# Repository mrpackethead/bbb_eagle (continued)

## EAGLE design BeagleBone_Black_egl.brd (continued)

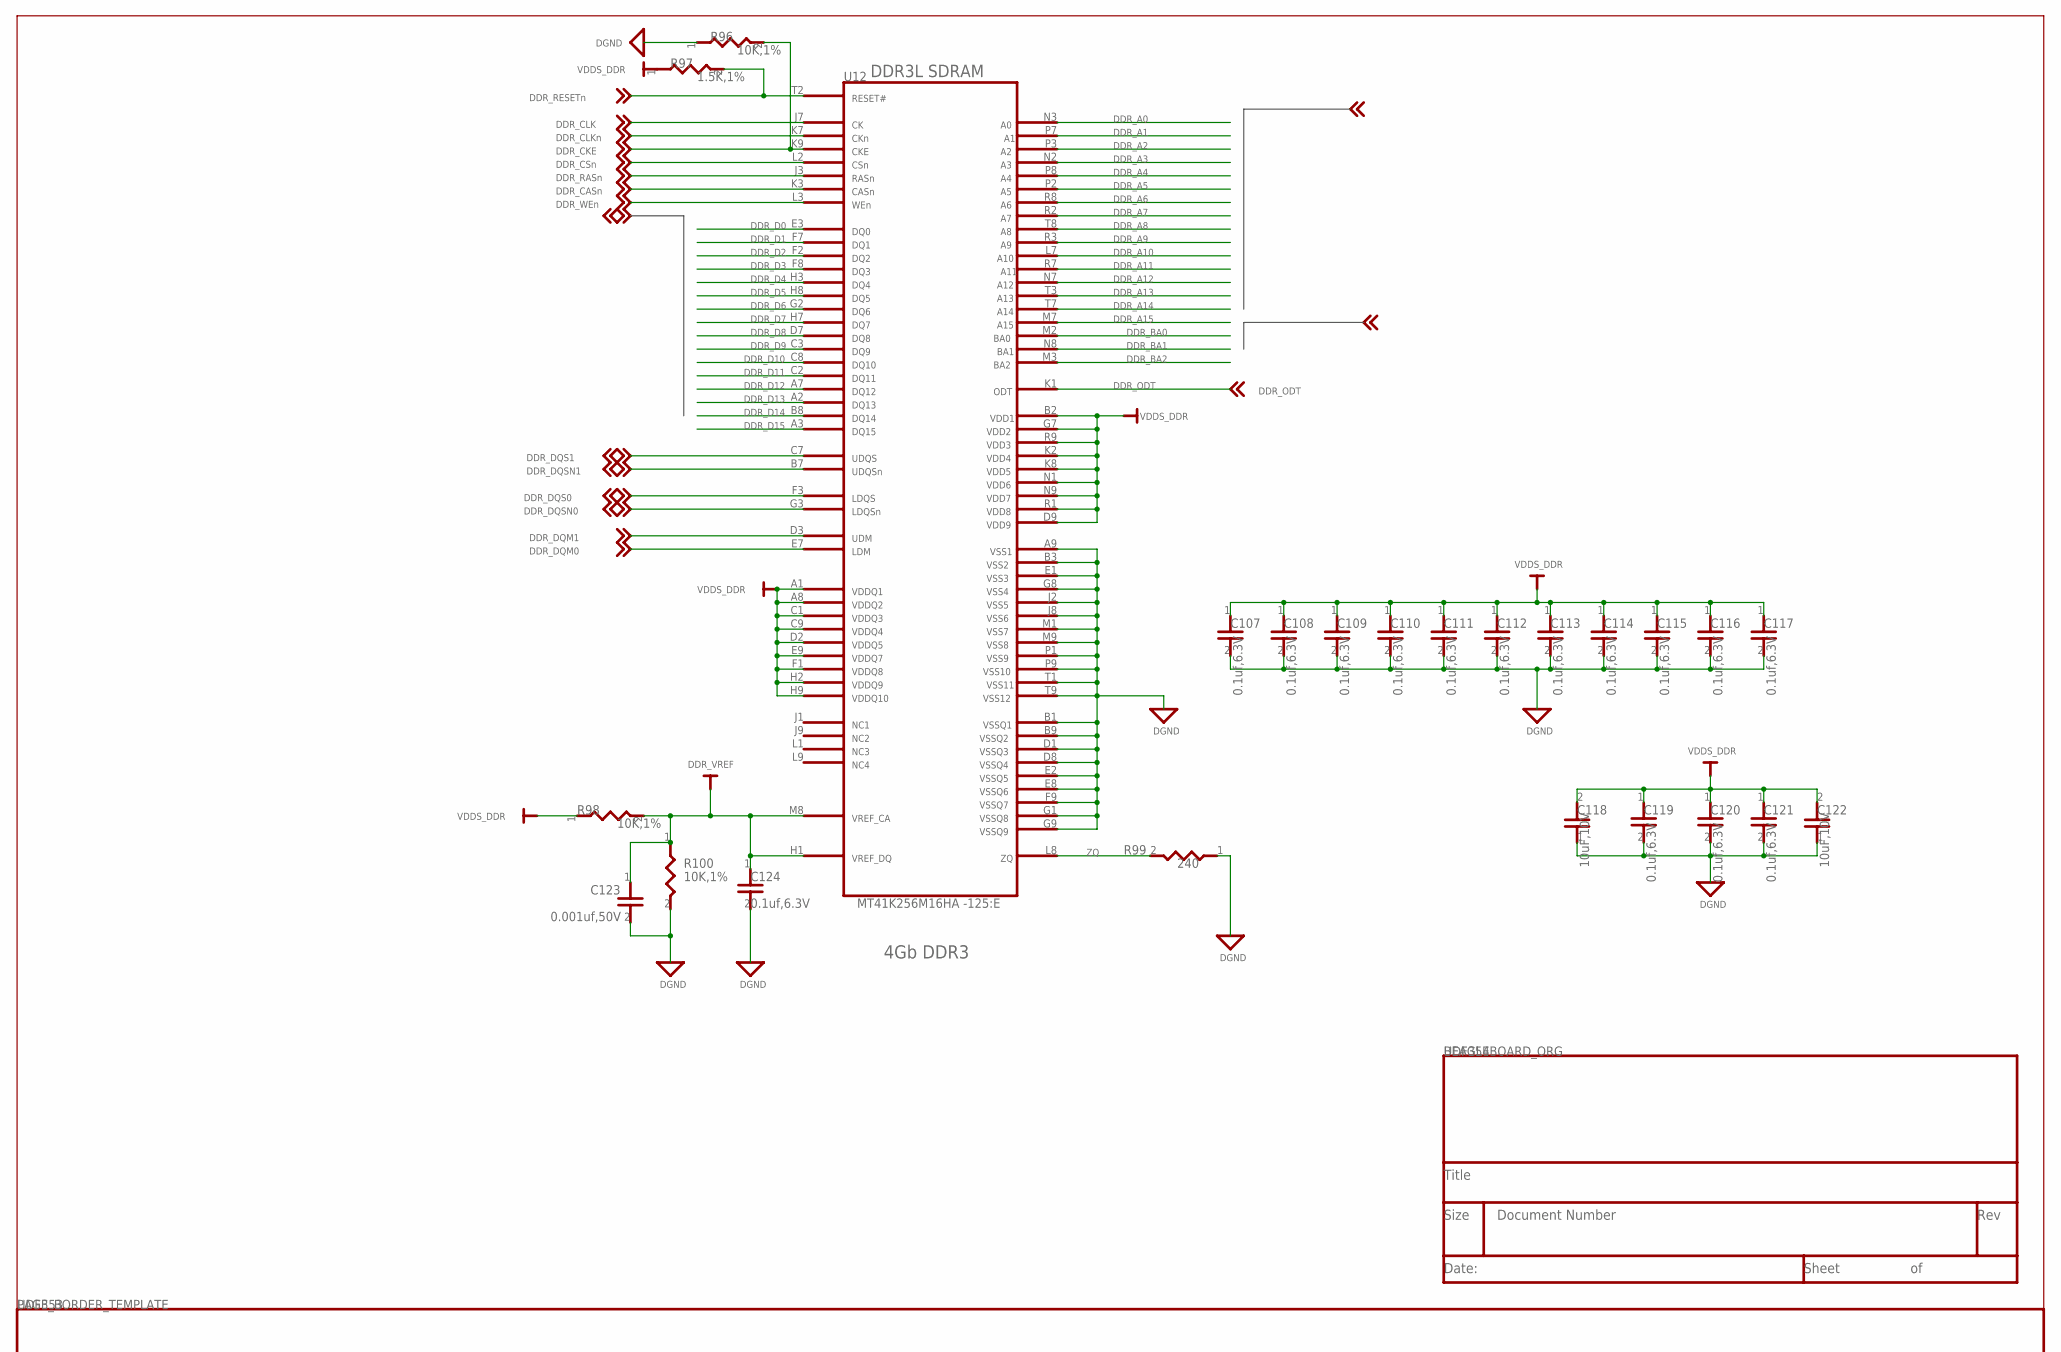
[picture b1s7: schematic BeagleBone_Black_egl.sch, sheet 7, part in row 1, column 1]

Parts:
C107, C108, C109, C110, C111, C112, C113, C114, C115, C116, C117, C119, C120, C121, C124: 0.1uf,6.3V; 402
C118, C122: 10uF,10V; 805
C123: 0.001uf,50V; 402
R96, R98, R100: 10K,1%; 402
R97: 1.5K,1%; 402
R99: 240; SM-7351-RES-0402
U12: MT41K256M16HA -125:E; BGA96_T9_P8_9X14

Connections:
DDR_A0: U12.N3 (8); also elsewhere on the board
DDR_A1: U12.P7 (9); also elsewhere on the board
DDR_A2: U12.P3 (10); also elsewhere on the board
DDR_A3: U12.N2 (11); also elsewhere on the board
DDR_A4: U12.P8 (12); also elsewhere on the board
DDR_A5: U12.P2 (13); also elsewhere on the board
DDR_A6: U12.R8 (14); also elsewhere on the board
DDR_A7: U12.R2 (15); also elsewhere on the board
DDR_A8: U12.T8 (16); also elsewhere on the board
DDR_A9: U12.R3 (17); also elsewhere on the board
DDR_A10: U12.L7 (18); also elsewhere on the board
DDR_A11: U12.R7 (19); also elsewhere on the board
DDR_A12: U12.N7 (20); also elsewhere on the board
DDR_A13: U12.T3 (21); also elsewhere on the board
DDR_A14: U12.T7 (22); also elsewhere on the board
DDR_A15: U12.M7 (84); also elsewhere on the board
DDR_BA0: U12.M2 (23); also elsewhere on the board
DDR_BA1: U12.N8 (24); also elsewhere on the board
DDR_BA2: U12.M3 (25); also elsewhere on the board
DDR_CASN: U12.K3 (6); also elsewhere on the board
DDR_CKE: R96.2, U12.K9 (3); also elsewhere on the board
DDR_CLK: U12.J7 (1); also elsewhere on the board
DDR_CLKN: U12.K7 (2); also elsewhere on the board
DDR_CSN: U12.L2 (4); also elsewhere on the board
DDR_D0: U12.E3 (26); also elsewhere on the board
DDR_D1: U12.F7 (27); also elsewhere on the board
DDR_D2: U12.F2 (28); also elsewhere on the board
DDR_D3: U12.F8 (29); also elsewhere on the board
DDR_D4: U12.H3 (30); also elsewhere on the board
DDR_D5: U12.H8 (31); also elsewhere on the board
DDR_D6: U12.G2 (32); also elsewhere on the board
DDR_D7: U12.H7 (33); also elsewhere on the board
DDR_D8: U12.D7 (57); also elsewhere on the board
DDR_D9: U12.C3 (96); also elsewhere on the board
DDR_D10: U12.C8 (58); also elsewhere on the board
DDR_D11: U12.C2 (59); also elsewhere on the board
DDR_D12: U12.A7 (61); also elsewhere on the board
DDR_D13: U12.A2 (63); also elsewhere on the board
DDR_D14: U12.B8 (60); also elsewhere on the board
DDR_D15: U12.A3 (62); also elsewhere on the board
DDR_DQM0: U12.E7 (53); also elsewhere on the board
DDR_DQM1: U12.D3 (52); also elsewhere on the board
DDR_DQS0: U12.F3 (56); also elsewhere on the board
DDR_DQS1: U12.C7 (55); also elsewhere on the board
DDR_DQSN0: U12.G3 (54); also elsewhere on the board
DDR_DQSN1: U12.B7 (51); also elsewhere on the board
DDR_ODT: U12.K1 (34); also elsewhere on the board
DDR_RASN: U12.J3 (5); also elsewhere on the board
DDR_RESETN: R97.2, U12.T2 (94); also elsewhere on the board
DDR_VREF: C123.1, C124.1, R98.2, R100.1, U12.H1 (71), U12.M8 (85); also elsewhere on the board
DDR_WEN: U12.L3 (7); also elsewhere on the board
DGND: C107.2, C108.2, C109.2, C110.2, C111.2, C112.2, C113.2, C114.2, C115.2, C116.2, C117.2, C118.1, C119.2, C120.2, C121.2, C122.1, C123.2, C124.2, R96.1, R99.1, R100.2, U12.A9 (35), U12.B1 (42), U12.B3 (36), U12.B9 (41), U12.D1 (40), U12.D8 (39), U12.E1 (37), U12.E2 (43), U12.E8 (65), U12.F9 (68), U12.G1 (69), U12.G8 (38), U12.G9 (70), U12.J2 (76), U12.J8 (77), U12.M1 (83), U12.M9 (86), U12.P1 (89), U12.P9 (90), U12.T1 (93), U12.T9 (95); also elsewhere on the board
VDDS_DDR: C107.1, C108.1, C109.1, C110.1, C111.1, C112.1, C113.1, C114.1, C115.1, C116.1, C117.1, C118.2, C119.1, C120.1, C121.1, C122.2, R97.1, R98.1, U12.A1 (44), U12.A8 (45), U12.B2 (49), U12.C1 (46), U12.C9 (47), U12.D2 (48), U12.D9 (64), U12.E9 (66), U12.F1 (67), U12.G7 (50), U12.H2 (72), U12.H9 (73), U12.K2 (78), U12.K8 (79), U12.N1 (87), U12.N9 (88), U12.R1 (91), U12.R9 (92); also elsewhere on the board
ZQ: R99.2, U12.L8 (81)

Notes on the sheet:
DDR3L SDRAM
4Gb DDR3
DGND
VDDS_DDR
DDR_A0
DDR_A1
DDR_A10
DDR_A11
DDR_A12
DDR_A13
DDR_A14
DDR_A15
DDR_A2
DDR_A3
DDR_A4
DDR_A5
DDR_A6
DDR_A7
DDR_A8
DDR_A9
DDR_BA0
DDR_BA1
DDR_BA2
DDR_CASn
DDR_CKE
DDR_CLK
DDR_CLKn
DDR_CSn
DDR_D0
DDR_D1
DDR_D10
DDR_D11
DDR_D12
DDR_D13
DDR_D14
DDR_D15
DDR_D2
DDR_D3
DDR_D4
DDR_D5

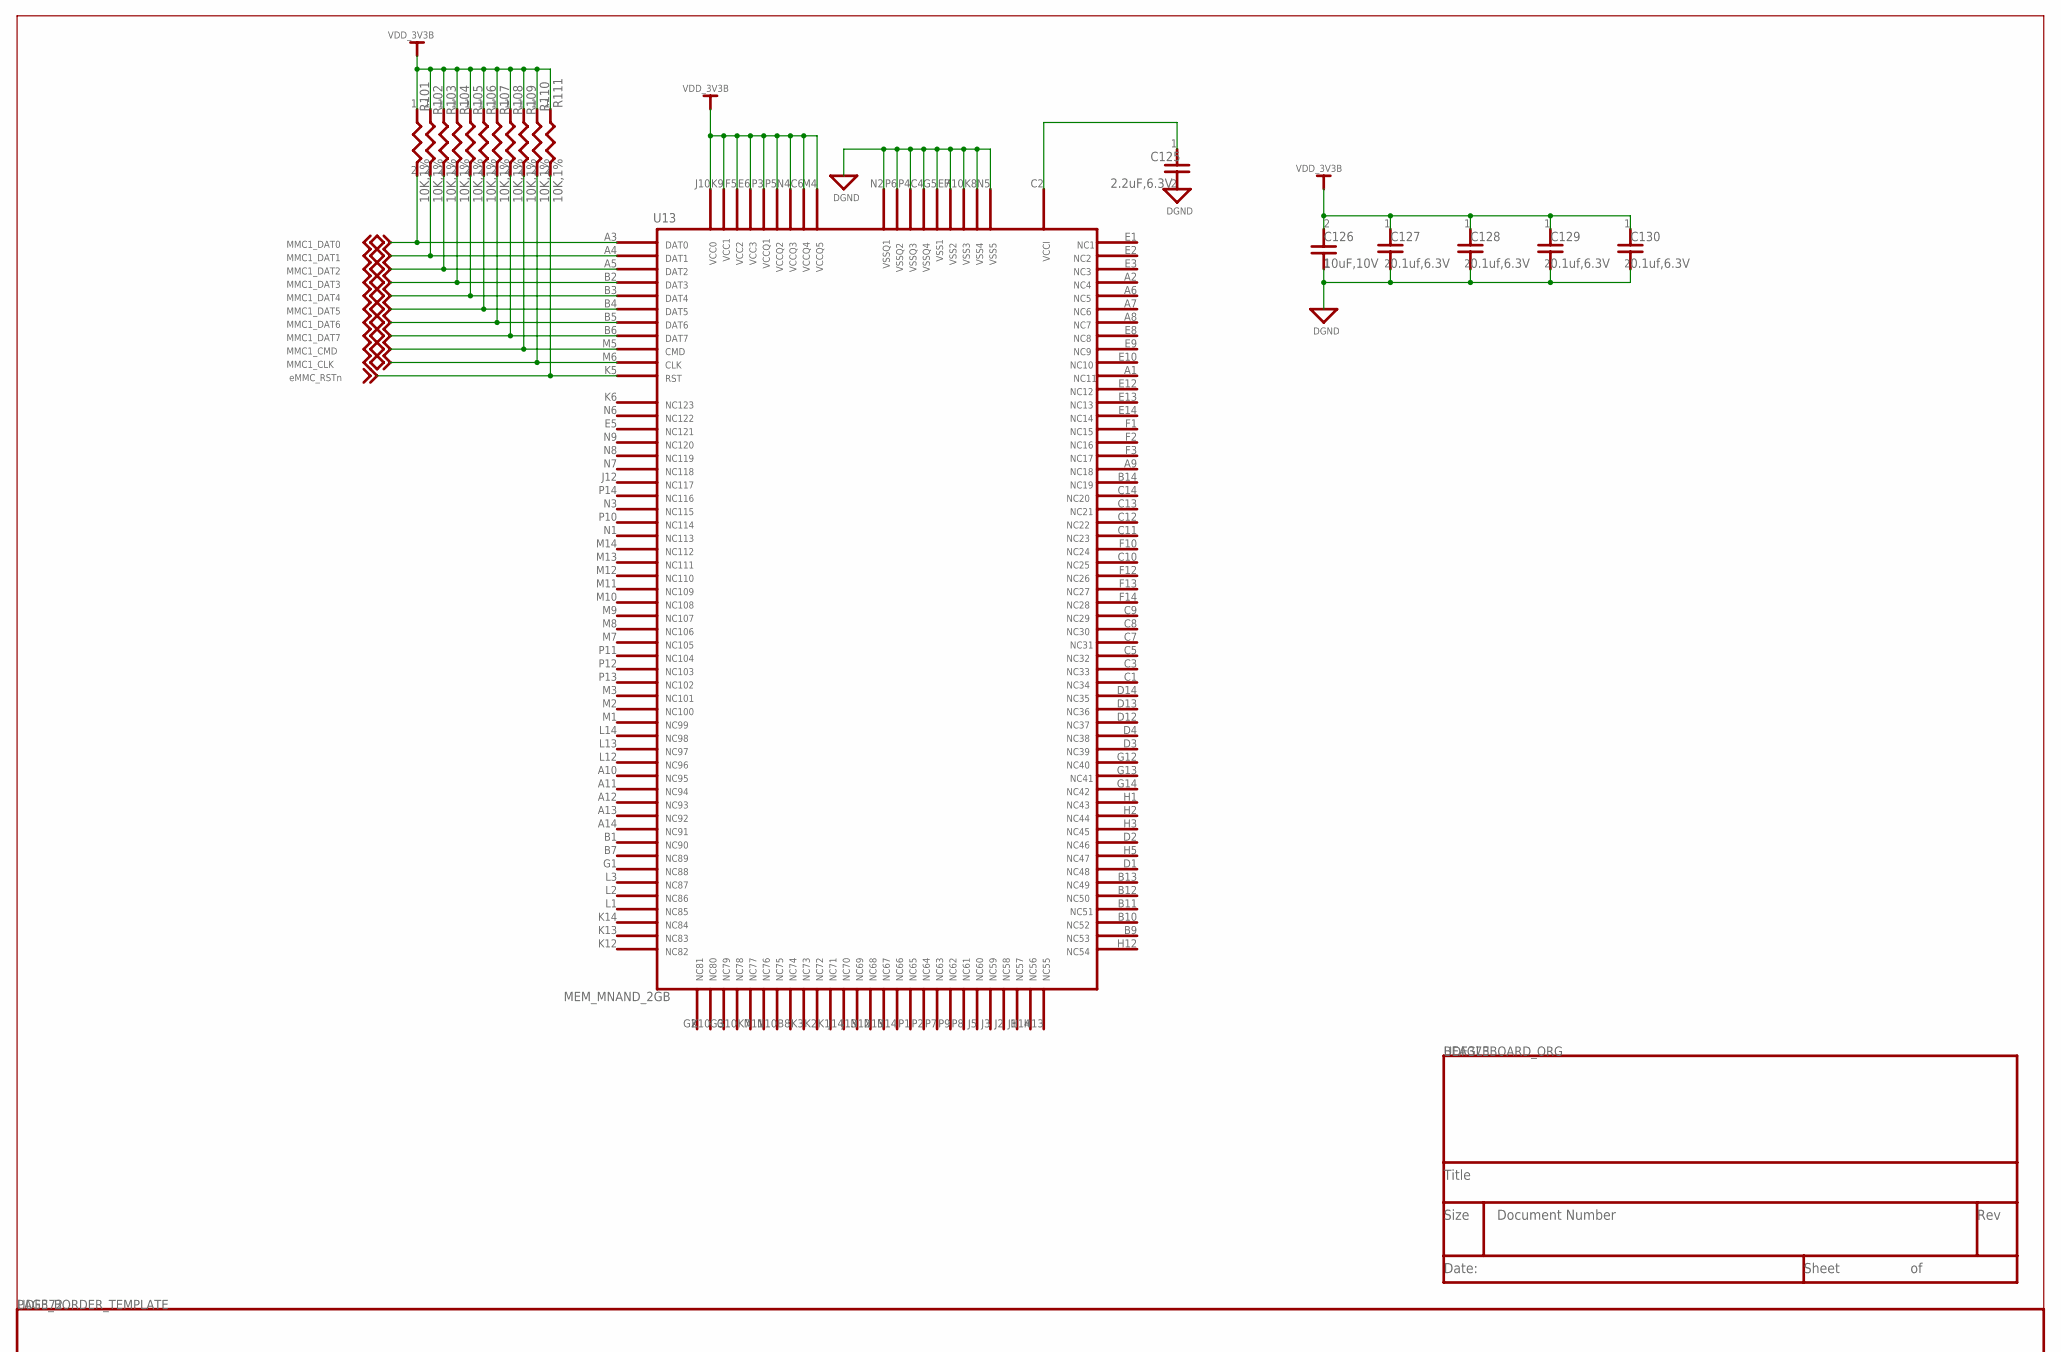
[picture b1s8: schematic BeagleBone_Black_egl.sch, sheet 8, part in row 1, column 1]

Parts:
C125: 2.2uF,6.3V; 402
C126: 10uF,10V; 805
C127, C128, C129, C130: 0.1uf,6.3V; 402
R101, R102, R103, R104, R105, R106, R107, R108, R109, R110, R111: 10K,1%; 402
U13: MEM_MNAND_2GB; BGA153_P14_P5_11P5X13

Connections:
DGND: C125.2, C126.1, C127.2, C128.2, C129.2, C130.2, U13.C4 (32), U13.E7 (54), U13.G5 (72), U13.H10 (81), U13.K8 (96), U13.N2 (123), U13.N5 (55), U13.P4 (138), U13.P6 (140); also elsewhere on the board
EMMC_RSTN: R111.2, U13.K5 (149); also elsewhere on the board
EMMC_VCCI: C125.1, U13.C2 (30)
MMC1_CLK: R110.2, U13.M6 (113); also elsewhere on the board
MMC1_CMD: R109.2, U13.M5 (112); also elsewhere on the board
MMC1_DAT0: R101.2, U13.A3 (3); also elsewhere on the board
MMC1_DAT1: R102.2, U13.A4 (4); also elsewhere on the board
MMC1_DAT2: R103.2, U13.A5 (5); also elsewhere on the board
MMC1_DAT3: R104.2, U13.B2 (16); also elsewhere on the board
MMC1_DAT4: R105.2, U13.B3 (17); also elsewhere on the board
MMC1_DAT5: R106.2, U13.B4 (18); also elsewhere on the board
MMC1_DAT6: R107.2, U13.B5 (19); also elsewhere on the board
MMC1_DAT7: R108.2, U13.B6 (20); also elsewhere on the board
VDD_3V3B: C126.2, C127.1, C128.1, C129.1, C130.1, R101.1, R102.1, R103.1, R104.1, R105.1, R106.1, R107.1, R108.1, R109.1, R110.1, R111.1, U13.C6 (34), U13.E6 (53), U13.F5 (65), U13.J10 (150), U13.K9 (97), U13.M4 (111), U13.N4 (125), U13.P3 (137), U13.P5 (139); also elsewhere on the board

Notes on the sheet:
DGND
VDD_3V3B
eMMC_RSTn
MMC1_CLK
MMC1_CMD
MMC1_DAT0
MMC1_DAT1
MMC1_DAT2
MMC1_DAT3
MMC1_DAT4
MMC1_DAT5
MMC1_DAT6
MMC1_DAT7

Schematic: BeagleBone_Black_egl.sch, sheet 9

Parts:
C131, C132, C135: 0.1uf,6.3V; 402
C133: 10uF,10V; 805
C134: 1uF,10V; 402
C136: 470pF,6.3V; 0402
C137, C138, C139, C140: 15pF,DNI; 402
C141: 0.022uF,10V; 402
C142, C143: 30pF,50V; 402
FB4: 150OHM800mA; SM-7351-IND-0805
P5: LPJ0011BBNL; RJ45-7499010211A
R112, R113, R114, R119: 1.5K,1%; 402
R115, R116, R117, R118, R135, R145: 10K,1%; 402
R120, R121, R122, R123: 49.9,1%; 402
R124: 10,1%,DNI; 402
R125, R126, R127, R128, R129, R131, R133, R134, R138, R139: 100,1%; 402
R130, R132: 470,5%; 402
R136: .1,0805; 805
R137, R142: 0,1%; 402
R140: 0,1%,DNI; 402
R141: 1M,1%,DNI; 402
R143: 10,1%; 402
R144: 12.1K,1%; 402
U14: LAN8710A; QFN32_5X5MM_EP3P3MM
Y3: 25.000MHz; XTAL150SMD_125X196

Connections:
CRS: R139.2, U14.14 (17)
DGND: C131.2, C132.2, C133.1, C134.2, C135.2, C136.2, C137.2, C138.2, C139.2, C140.2, C141.2, C142.2, C143.2, P5.8 (11), R115.2, R116.2, R117.2, R118.2, R130.1, R132.1, R135.2, R136.1, R144.2, R145.2, U14.33 (21); also elsewhere on the board
ETH_TXD4: R145.1, U14.18 (31)
GND_EARTH: P5.13 (12), P5.14 (13), R136.2; also elsewhere on the board
GRNA: P5.9 (10), U14.3 (33)
GRN_C: P5.10 (9), R132.2
MDIO_CLK: U14.17 (2); also elsewhere on the board
MDIO_DATA: R119.2, U14.16 (1); also elsewhere on the board
MII1_COL: R138.1; also elsewhere on the board
MII1_CRS_DV: R139.1; also elsewhere on the board
MII1_REFCLK: R124.1, R140.1; also elsewhere on the board
MII1_RXCLK: R131.1; also elsewhere on the board
MII1_RXD0: R128.1; also elsewhere on the board
MII1_RXD1: R127.1; also elsewhere on the board
MII1_RXD2: R126.1; also elsewhere on the board
MII1_RXD3: R125.1; also elsewhere on the board
MII1_RXDV: R129.1; also elsewhere on the board
MII1_RXERR: R133.1; also elsewhere on the board
MII1_TXCLK: R134.1; also elsewhere on the board
MII1_TXD0: U14.22 (12); also elsewhere on the board
MII1_TXD1: U14.23 (13); also elsewhere on the board
MII1_TXD2: U14.24 (14); also elsewhere on the board
MII1_TXD3: U14.25 (15); also elsewhere on the board
MII1_TXEN: U14.21 (11); also elsewhere on the board
MODE2: R113.1, R138.2, U14.15 (16)
PHYX: C142.1, R143.2, Y3.2
PHY_VDDCR: C134.1, C136.1, U14.6 (26)
PHY_XTAL1: C143.1, R141.2, R142.1, Y3.1
PHY_XTAL2: R141.1, R143.1, U14.4 (20)
RBIAS: R144.1, U14.32 (22)
RCLKIN: R140.2, R142.2, U14.5 (19)
REFCLKO: R118.1, R124.2, R131.2, U14.7 (8)
RXD0\MODE0\: R112.1, R128.2, U14.11 (6)
RXD1\MODE1\: R114.1, R127.2, U14.10 (5)
RXD2\RMIISEL\: R117.1, R126.2, U14.9 (4)
RXD3\PHYAD2\: R116.1, R125.2, U14.8 (3)
RXDV: R129.2, U14.26 (7)
RXER\PHYAD0\: R115.1, R133.2, U14.13 (9)
RXN: C138.1, P5.2 (5), R121.1, U14.30 (28)
RXP: C137.1, P5.1 (4), R120.1, U14.31 (27)
SYS_RESETN: U14.19 (18); also elsewhere on the board
TCT_RCT: C141.1, P5.4 (6), P5.5 (1), R137.1
TXCLK: R134.2, U14.20 (10)
TXN: C140.1, P5.6 (3), R123.1, U14.28 (29)
TXP: C139.1, P5.3 (2), R122.1, U14.29 (30)
VDD_3V3B: C135.1, FB4.1, R112.2, R113.2, R114.2, R119.1, U14.12 (23); also elsewhere on the board
VDD_PHYA: C131.1, C132.1, C133.2, FB4.2, R120.2, R121.2, R122.2, R123.2, R137.2, U14.1 (25), U14.27 (24)
YELA: P5.12 (8), R135.1, U14.2 (32)
YEL_C: P5.11 (7), R130.2

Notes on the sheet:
ESD_RING
ACTIVE WHEN LINK PRESENT.
BLINKS OFF DURING ACTIVITY.
ACTIVE WHEN AT 100MB
ETHERNET
CONNECTOR
DGND
GND_EARTH
VDD_3V3B
SYS_RESETn
MDIO_CLK
MDIO_DATA
MII1_COL
MII1_CRS_DV
MII1_REFCLK
MII1_RXCLK
MII1_RXD0
MII1_RXD1
MII1_RXD2
MII1_RXD3
MII1_RXDV
MII1_RXERR
MII1_TXCLK
MII1_TXD0
MII1_TXD1
MII1_TXD2
MII1_TXD3
MII1_TXEN
CRS
ETH_TXD4
GRNA
GRN_C
MODE2
PHYX
PHY_VDDCR
PHY_XTAL1
PHY_XTAL2
RBIAS
RCLKIN
REFCLKO

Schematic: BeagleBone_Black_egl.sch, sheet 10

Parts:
C144, C146, C148, C151: 2.2uF,6.3V; 402
C145, C147, C149, C150: 0.1uf,6.3V; 402
C156, C157, C160, C161, C162, C163, C164, C165, C166, C167, C168, C169, C170, C171, C172, C173: 47pf,6.3V; 402
D6, D7: IP4283CZ10-TT; TSSOP10
D8: RB751V40,115; SOD323
FB5: 150OHM800mA; SM-7351-IND-0805
P6: 10118241-001RLF; CONN19_HDMI
R146: 1.5K,1%; 402
R147: 1.5K1%; 402
R148, R158: 10K,1%; 402
R149: 0,1%; 402
R166: 27K,1%; 402
RT1: PTC_RXEF010; POLYSW200-5638-310
U11: TDA19988; QFN64S9X9P5

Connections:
12MHZ: U11.27 (59); also elsewhere on the board
DGND: C144.2, C145.2, C146.2, C147.2, C148.2, C149.2, C150.2, C151.2, C156.2, C157.2, C160.2, C161.2, C162.2, C163.2, C164.2, C165.2, C166.2, C167.2, C168.2, C169.2, C170.2, C171.2, C172.2, C173.2, D6.3 (6), D6.8 (3), D7.3 (6), D7.8 (3), P6.4 (3), P6.7 (5), P6.10 (8), P6.13 (12), P6.16 (17), R148.2, R149.2, U11.8 (10), U11.9, U11.16 (19), U11.17 (18), U11.18 (17), U11.19 (50), U11.53 (57), U11.54 (58), U11.61 (3), U11.62 (2), U11.63 (1), U11.65; also elsewhere on the board
DVI_+5V: P6.19 (18), R146.1, R147.1, RT1.2
GND_EARTH: P6.20, P6.21, P6.22, P6.23; also elsewhere on the board
HDMI_1V8: C144.1, C145.1, C146.1, C147.1, C148.1, C149.1, C150.1, C151.1, FB5.1, U11.5 (55), U11.14 (49), U11.29 (56), U11.35 (53), U11.36 (54), U11.41 (61), U11.46 (62), U11.47 (52), U11.48 (63), U11.55 (64)
HDMI_CEC: D8.1 (2), P6.15 (13), U11.30 (34)
HDMI_CEC_D: D8.2 (1), R166.1
HDMI_DSCL: P6.17 (15), R146.2, U11.33 (28)
HDMI_DSDA: P6.18 (16), R147.2, U11.32 (29)
HDMI_HPD: P6.1 (19), U11.31 (32)
HDMI_INT: R158.2, U11.50 (33); also elsewhere on the board
HDMI_SWING: R148.1, U11.34 (47)
HDMI_TX0+: D6.2, P6.9 (7), U11.40 (37)
HDMI_TX0-: D6.1, P6.11 (9), U11.39 (38)
HDMI_TX1+: D7.5, P6.6 (4), U11.43 (39)
HDMI_TX1-: D7.4, P6.8 (6), U11.42 (40)
HDMI_TX2+: D7.2, P6.3 (1), U11.45 (41)
HDMI_TX2-: D7.1, P6.5 (2), U11.44 (42)
HDMI_TXC+: D6.4, P6.12 (10), U11.38 (35)
HDMI_TXC-: D6.5, P6.14 (11), U11.37 (36)
I2C0_SCL: U11.52 (30); also elsewhere on the board
I2C0_SDA: U11.51 (31); also elsewhere on the board
LCD_DATA0: C173.1, U11.15 (20); also elsewhere on the board
LCD_DATA1: C171.1, U11.13 (21); also elsewhere on the board
LCD_DATA2: C172.1, U11.12 (22); also elsewhere on the board
LCD_DATA3: C170.1, U11.11 (23); also elsewhere on the board
LCD_DATA4: C169.1, U11.10 (24); also elsewhere on the board
LCD_DATA5: C163.1, U11.7 (11); also elsewhere on the board
LCD_DATA6: C162.1, U11.6 (12); also elsewhere on the board
LCD_DATA7: C161.1, U11.3 (13); also elsewhere on the board
LCD_DATA8: C160.1, U11.2 (14); also elsewhere on the board
LCD_DATA9: C157.1, U11.1 (15); also elsewhere on the board
LCD_DATA10: C156.1, U11.64 (16); also elsewhere on the board
LCD_DATA11: C168.1, U11.60 (4); also elsewhere on the board
LCD_DATA12: C167.1, U11.59 (5); also elsewhere on the board
LCD_DATA13: C166.1, U11.58 (6); also elsewhere on the board
LCD_DATA14: C165.1, U11.57 (7); also elsewhere on the board
LCD_DATA15: C164.1, U11.56 (8); also elsewhere on the board
LCD_DE: U11.20 (27); also elsewhere on the board
LCD_HSYNC: U11.22 (26); also elsewhere on the board
LCD_PCLK: U11.4 (43); also elsewhere on the board
LCD_VSYNC: U11.21 (25); also elsewhere on the board
N21667305: R149.1, U11.49 (51)
SPI1_CS0: U11.25 (46); also elsewhere on the board
SPI1_D0: U11.24 (45); also elsewhere on the board
SPI1_SCLK: U11.23 (44); also elsewhere on the board
SYS_5V: RT1.1; also elsewhere on the board
VDD_1V8: FB5.2; also elsewhere on the board
VDD_3V3B: R158.1, R166.2; also elsewhere on the board

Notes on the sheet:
GREEN
RED
BLUE
McASP0_ACLKX (Pin A13 Mode 0)
McASP0_AXR2 (Pin C12 Mode 2)
McASP0_FSX (Pin B13 Mode 0)
DGND
GND_EARTH
I2C0_SCL
I2C0_SDA
SYS_5V
VDD_1V8
VDD_3V3B
12MHZ
HDMI_INT
LCD_DATA0
LCD_DATA1
LCD_DATA10
LCD_DATA11
LCD_DATA12
LCD_DATA13
LCD_DATA14
LCD_DATA15
LCD_DATA2
LCD_DATA3
LCD_DATA4
LCD_DATA5
LCD_DATA6
LCD_DATA7
LCD_DATA8
LCD_DATA9
LCD_DE
LCD_HSYNC
LCD_PCLK
LCD_VSYNC
SPI1_CS0
SPI1_D0
SPI1_SCLK
HDMI_1V8
HDMI_CEC

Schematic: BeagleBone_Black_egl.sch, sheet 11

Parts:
C152, C154: 0.1uf,6.3V; 402
C153: 10uF,10V; 805
P8, P9: FEMALE HEADER 2x23; HEADER23X2
P10: SCHA5B0200; SD-MICRO-SCHA5B0300
R150, R151, R152, R153, R154, R155, R156, R157: 10K,1%; 402
TP4: TESTPT1; TP1-8040
U7: 24LC32A; SOT23-5

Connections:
AIN0: P9.39 (43); also elsewhere on the board
AIN1: P9.40 (20); also elsewhere on the board
AIN2: P9.37 (42); also elsewhere on the board
AIN3: P9.38 (19); also elsewhere on the board
AIN4: P9.33 (40); also elsewhere on the board
AIN5: P9.36 (18); also elsewhere on the board
AIN6: P9.35 (41); also elsewhere on the board
CLKOUT2: P9.41 (44); also elsewhere on the board
DGND: C152.2, C153.2, C154.2, P8.1 (24), P8.2 (1), P9.1 (24), P9.2 (1), P9.43 (45), P9.44 (22), P9.45 (46), P9.46 (23), P10.6, P10.9, U7.2 (4); also elsewhere on the board
EHRPWM1A: P9.14 (7); also elsewhere on the board
EHRPWM1B: P9.16 (8); also elsewhere on the board
EHRPWM2A: P8.19 (33); also elsewhere on the board
EHRPWM2B: P8.13 (30); also elsewhere on the board
GNDA_ADC: P9.34 (17); also elsewhere on the board
GND_EARTH: P10.11, P10.12, P10.13, P10.14, P10.15, P10.16; also elsewhere on the board
GPIO0_7: P9.42 (21); also elsewhere on the board
GPIO0_26: P8.14 (7); also elsewhere on the board
GPIO0_27: P8.17 (32); also elsewhere on the board
GPIO1_12: P8.12 (6); also elsewhere on the board
GPIO1_13: P8.11 (29); also elsewhere on the board
GPIO1_14: P8.16 (8); also elsewhere on the board
GPIO1_15: P8.15 (31); also elsewhere on the board
GPIO1_16: P9.15 (31); also elsewhere on the board
GPIO1_17: P9.23 (35); also elsewhere on the board
GPIO1_28: P9.12 (6); also elsewhere on the board
GPIO1_29: P8.26 (13); also elsewhere on the board
GPIO2_1: P8.18 (9); also elsewhere on the board
GPIO3_19: P9.27 (37); also elsewhere on the board
GPIO3_21: P9.25 (36); also elsewhere on the board
I2C0_SCL: U7.1; also elsewhere on the board
I2C0_SDA: U7.3 (2); also elsewhere on the board
I2C1_SCL: P9.17 (32); also elsewhere on the board
I2C1_SDA: P9.18 (9); also elsewhere on the board
I2C2_SCL: P9.19 (33); also elsewhere on the board
I2C2_SDA: P9.20 (10); also elsewhere on the board
LCD_DATA0: P8.45 (46); also elsewhere on the board
LCD_DATA1: P8.46 (23); also elsewhere on the board
LCD_DATA2: P8.43 (45); also elsewhere on the board
LCD_DATA3: P8.44 (22); also elsewhere on the board
LCD_DATA4: P8.41 (44); also elsewhere on the board
LCD_DATA5: P8.42 (21); also elsewhere on the board
LCD_DATA6: P8.39 (43); also elsewhere on the board
LCD_DATA7: P8.40 (20); also elsewhere on the board
LCD_DATA8: P8.37 (42); also elsewhere on the board
LCD_DATA9: P8.38 (19); also elsewhere on the board
LCD_DATA10: P8.36 (18); also elsewhere on the board
LCD_DATA11: P8.34 (17); also elsewhere on the board
LCD_DATA12: P8.35 (41); also elsewhere on the board
LCD_DATA13: P8.33 (40); also elsewhere on the board
LCD_DATA14: P8.31 (39); also elsewhere on the board
LCD_DATA15: P8.32 (16); also elsewhere on the board
LCD_DE: P8.30 (15); also elsewhere on the board
LCD_HSYNC: P8.29 (38); also elsewhere on the board
LCD_PCLK: P8.28 (14); also elsewhere on the board
LCD_VSYNC: P8.27 (37); also elsewhere on the board
MMC0_CD: P10.10, R157.1; also elsewhere on the board
MMC0_CLKO: P10.5, R152.2; also elsewhere on the board
MMC0_CMD: P10.3, R151.2; also elsewhere on the board
MMC0_DAT0: P10.7, R153.2; also elsewhere on the board
MMC0_DAT1: P10.8, R154.2; also elsewhere on the board
MMC0_DAT2: P10.1, R150.2; also elsewhere on the board
MMC0_DAT3: P10.2, R155.2; also elsewhere on the board
MMC1_CLK: P8.21 (34); also elsewhere on the board
MMC1_CMD: P8.20 (10); also elsewhere on the board
MMC1_DAT0: P8.25 (36); also elsewhere on the board
MMC1_DAT1: P8.24 (12); also elsewhere on the board
MMC1_DAT2: P8.5 (26); also elsewhere on the board
MMC1_DAT3: P8.6 (3); also elsewhere on the board
MMC1_DAT4: P8.23 (35); also elsewhere on the board
MMC1_DAT5: P8.22 (11); also elsewhere on the board
MMC1_DAT6: P8.3 (25); also elsewhere on the board
MMC1_DAT7: P8.4 (2); also elsewhere on the board
PWR_BUT: P9.9 (28); also elsewhere on the board
SPI1_CS0: P9.28 (14); also elsewhere on the board
SPI1_D0: P9.29 (38); also elsewhere on the board
SPI1_D1: P9.30 (15); also elsewhere on the board
SPI1_SCLK: P9.31 (39); also elsewhere on the board
SYS_5V: P9.7 (27), P9.8 (4); also elsewhere on the board
SYS_RESETN: P9.10 (5); also elsewhere on the board
TIMER4: P8.7 (27); also elsewhere on the board
TIMER5: P8.9 (28); also elsewhere on the board
TIMER6: P8.10 (5); also elsewhere on the board
TIMER7: P8.8 (4); also elsewhere on the board
UART1_RXD: P9.26 (13); also elsewhere on the board
UART1_TXD: P9.24 (12); also elsewhere on the board
UART2_RXD: P9.22 (11); also elsewhere on the board
UART2_TXD: P9.21 (34); also elsewhere on the board
UART4_RXD: P9.11 (29); also elsewhere on the board
UART4_TXD: P9.13 (30); also elsewhere on the board
VDD_3V3A: C152.1, R156.1, U7.4 (3); also elsewhere on the board
VDD_3V3B: C153.1, C154.1, P9.3 (25), P9.4 (2), P10.4, R150.1, R151.1, R152.1, R153.1, R154.1, R155.1, R157.2; also elsewhere on the board
VDD_5V: P9.5 (26), P9.6 (3); also elsewhere on the board
VDD_ADC: P9.32 (16); also elsewhere on the board
WP: R156.2, TP4.1, U7.5

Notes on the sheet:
EXPANSION HEADER
Board ID
256KX8
uSD CONNECTOR
CAUTION: USED ON BOARD
DGND
GND_EARTH
I2C0_SCL
I2C0_SDA
PWR_BUT
SYS_5V
VDD_3V3A
VDD_3V3B
VDD_5V
CLKOUT2
EHRPWM1A
EHRPWM1B
EHRPWM2A
EHRPWM2B
GPIO0_26
GPIO0_27
GPIO1_12
GPIO1_13
GPIO1_14
GPIO1_15
GPIO1_16
GPIO1_17
GPIO1_28
GPIO1_29
GPIO2_1
GPIO3_21
MMC0_CD
MMC0_CLKO
MMC0_CMD
MMC0_DAT0
MMC0_DAT1
MMC0_DAT2
MMC0_DAT3
MMC1_CLK
MMC1_CMD

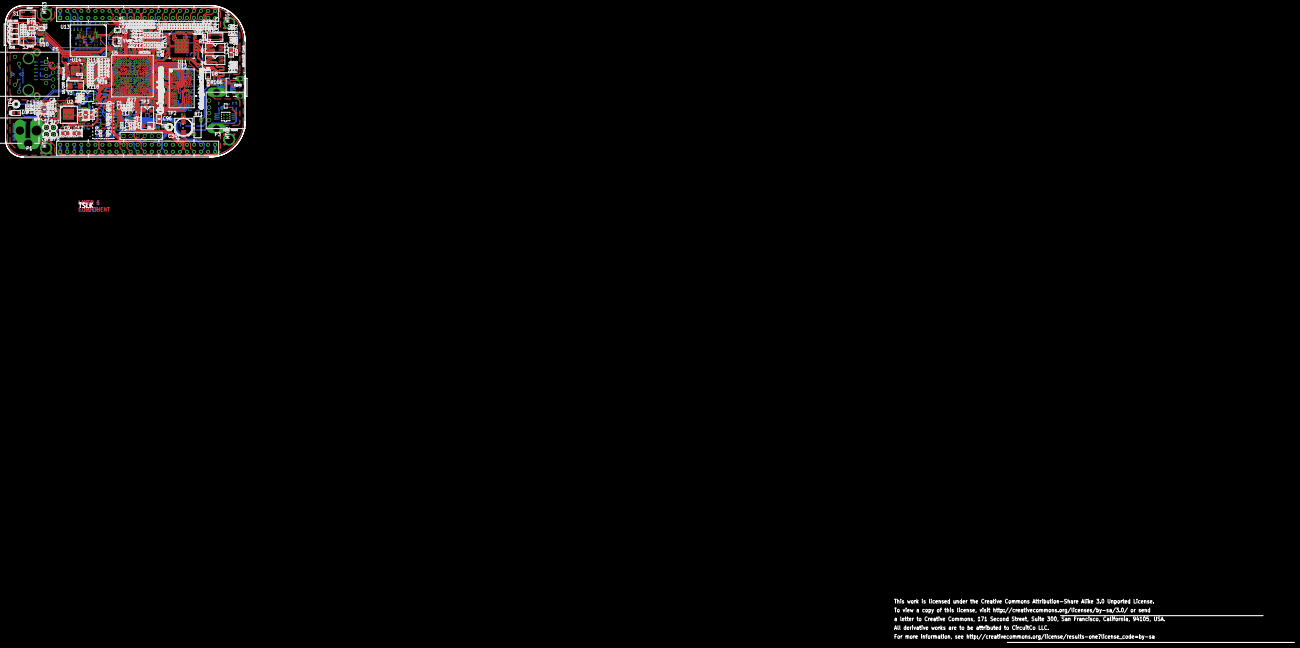
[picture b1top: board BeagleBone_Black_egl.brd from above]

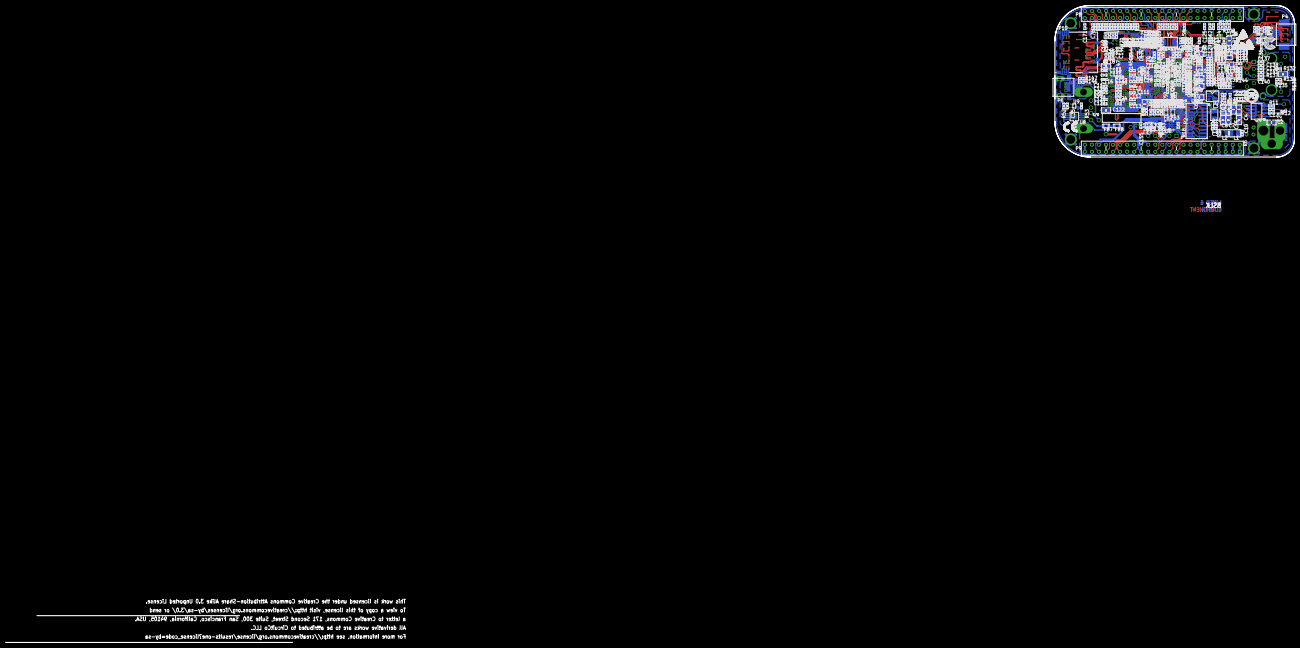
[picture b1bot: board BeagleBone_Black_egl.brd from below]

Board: 6 copper layers, 86.4 x 54.6 mm, 389 parts (253 on the bottom side), 310 nets.

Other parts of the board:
FZ3, FZ4, FZ5, FZ6, FZ7, FZ8: FUD40C
MECH1, MECH2: CREATIVE_COMMONS_NOTE

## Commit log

2013-08-05 first copy of files
    BBB in Ealge file - raw conversion
